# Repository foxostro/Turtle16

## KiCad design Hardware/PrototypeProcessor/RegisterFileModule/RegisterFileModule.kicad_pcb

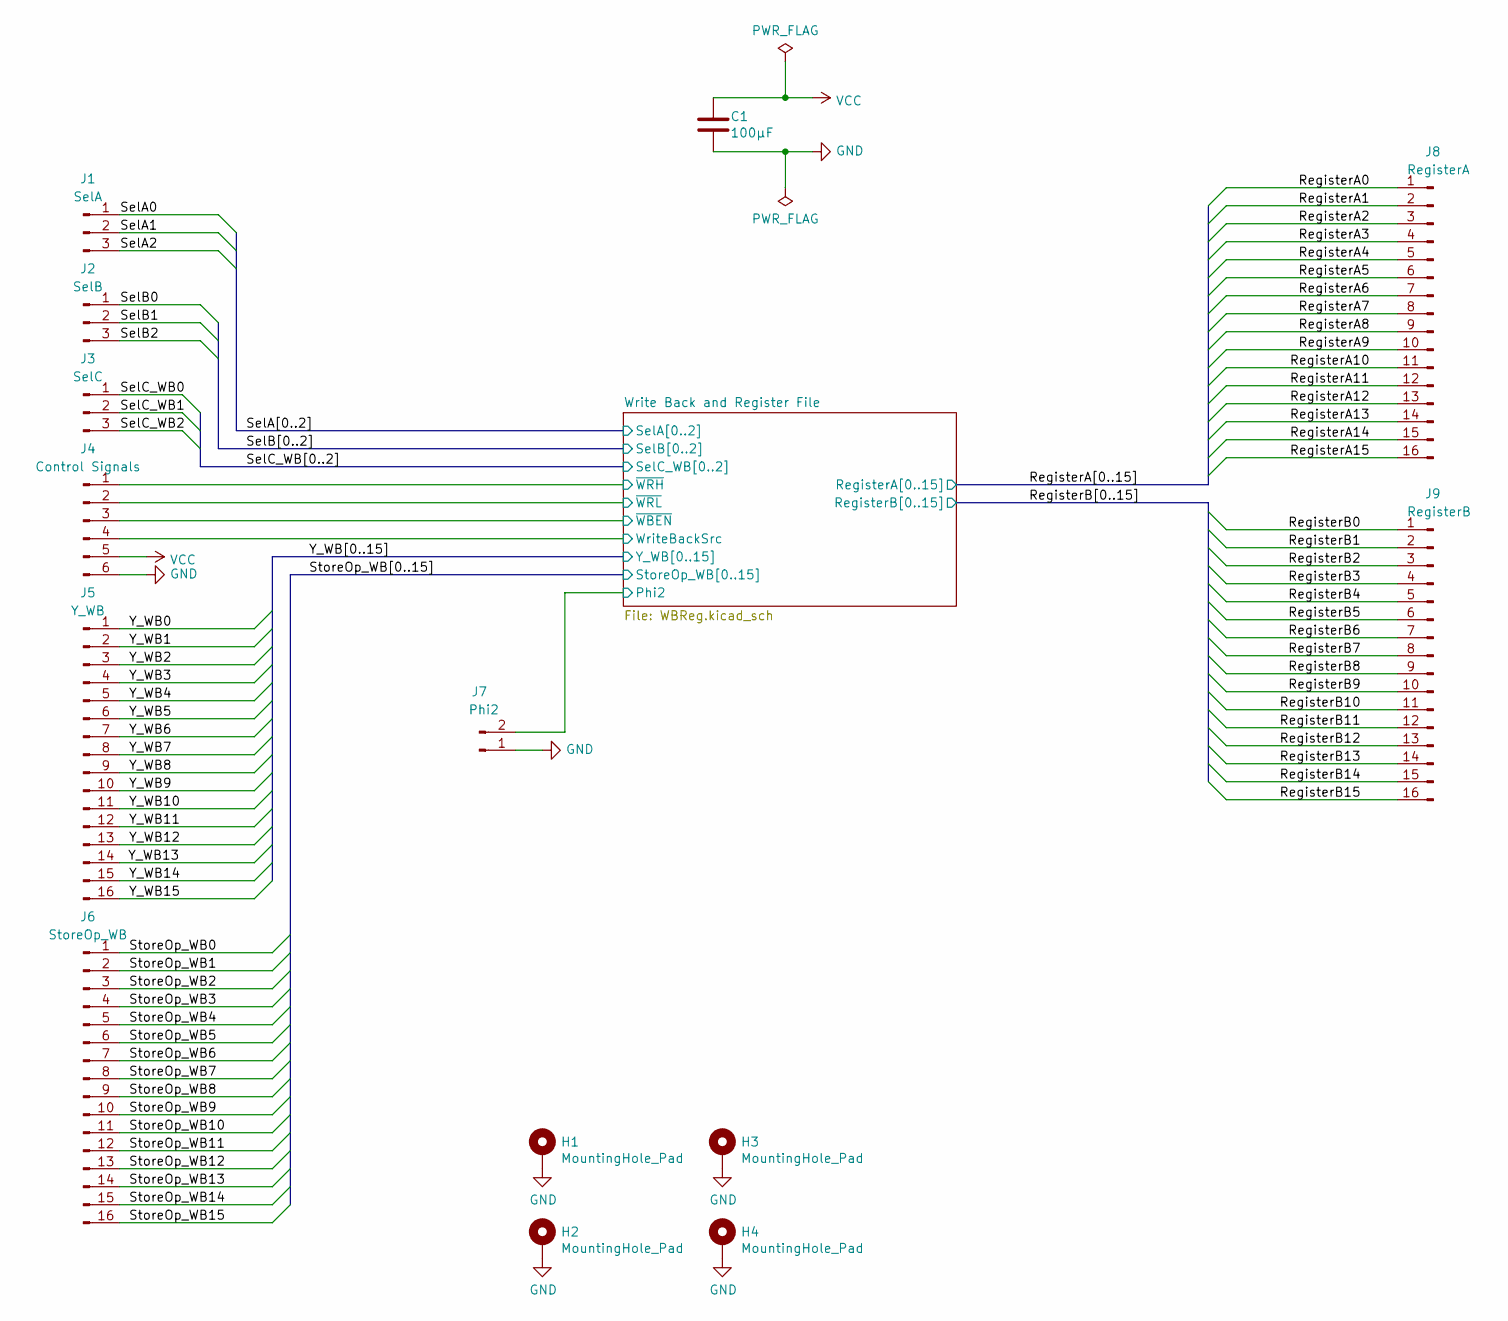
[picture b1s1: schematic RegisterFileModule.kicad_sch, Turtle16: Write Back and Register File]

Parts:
C1: 100µF; C_1206_3216Metric_Pad1.33x1.80mm_HandSolder
H1, H2, H3, H4: MountingHole_Pad; MountingHole_3.2mm_M3_Pad
J1: SelA; PinHeader_1x03_P2.54mm_Vertical
J2: SelB; PinHeader_1x03_P2.54mm_Vertical
J3: SelC; PinHeader_1x03_P2.54mm_Vertical
J4: Control Signals; PinHeader_1x06_P2.54mm_Vertical
J5: Y_WB; PinHeader_1x16_P2.54mm_Vertical
J6: StoreOp_WB; PinHeader_1x16_P2.54mm_Vertical
J7: Phi2; PinHeader_1x02_P2.54mm_Vertical
J8: RegisterA; PinHeader_1x16_P2.54mm_Vertical
J9: RegisterB; PinHeader_1x16_P2.54mm_Vertical

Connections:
/RegisterA0: J8.1; also elsewhere on the board
/RegisterA1: J8.2; also elsewhere on the board
/RegisterA2: J8.3; also elsewhere on the board
/RegisterA3: J8.4; also elsewhere on the board
/RegisterA4: J8.5; also elsewhere on the board
/RegisterA5: J8.6; also elsewhere on the board
/RegisterA6: J8.7; also elsewhere on the board
/RegisterA7: J8.8; also elsewhere on the board
/RegisterA8: J8.9; also elsewhere on the board
/RegisterA9: J8.10; also elsewhere on the board
/RegisterA10: J8.11; also elsewhere on the board
/RegisterA11: J8.12; also elsewhere on the board
/RegisterA12: J8.13; also elsewhere on the board
/RegisterA13: J8.14; also elsewhere on the board
/RegisterA14: J8.15; also elsewhere on the board
/RegisterA15: J8.16; also elsewhere on the board
/RegisterB0: J9.1; also elsewhere on the board
/RegisterB1: J9.2; also elsewhere on the board
/RegisterB2: J9.3; also elsewhere on the board
/RegisterB3: J9.4; also elsewhere on the board
/RegisterB4: J9.5; also elsewhere on the board
/RegisterB5: J9.6; also elsewhere on the board
/RegisterB6: J9.7; also elsewhere on the board
/RegisterB7: J9.8; also elsewhere on the board
/RegisterB8: J9.9; also elsewhere on the board
/RegisterB9: J9.10; also elsewhere on the board
/RegisterB10: J9.11; also elsewhere on the board
/RegisterB11: J9.12; also elsewhere on the board
/RegisterB12: J9.13; also elsewhere on the board
/RegisterB13: J9.14; also elsewhere on the board
/RegisterB14: J9.15; also elsewhere on the board
/RegisterB15: J9.16; also elsewhere on the board
/SelA0: J1.1; also elsewhere on the board
/SelA1: J1.2; also elsewhere on the board
/SelA2: J1.3; also elsewhere on the board
/SelB0: J2.1; also elsewhere on the board
/SelB1: J2.2; also elsewhere on the board
/SelB2: J2.3; also elsewhere on the board
/SelC_WB0: J3.1; also elsewhere on the board
/SelC_WB1: J3.2; also elsewhere on the board
/SelC_WB2: J3.3; also elsewhere on the board
/StoreOp_WB0: J6.1; also elsewhere on the board
/StoreOp_WB1: J6.2; also elsewhere on the board
/StoreOp_WB2: J6.3; also elsewhere on the board
/StoreOp_WB3: J6.4; also elsewhere on the board
/StoreOp_WB4: J6.5; also elsewhere on the board
/StoreOp_WB5: J6.6; also elsewhere on the board
/StoreOp_WB6: J6.7; also elsewhere on the board
/StoreOp_WB7: J6.8; also elsewhere on the board
/StoreOp_WB8: J6.9; also elsewhere on the board
/StoreOp_WB9: J6.10; also elsewhere on the board
/StoreOp_WB10: J6.11; also elsewhere on the board
/StoreOp_WB11: J6.12; also elsewhere on the board
/StoreOp_WB12: J6.13; also elsewhere on the board
/StoreOp_WB13: J6.14; also elsewhere on the board
/StoreOp_WB14: J6.15; also elsewhere on the board
/StoreOp_WB15: J6.16; also elsewhere on the board
/Write Back and Register File/Phi2: J7.2; also elsewhere on the board
/Write Back and Register File/WriteBackSrc: J4.4; also elsewhere on the board
/Write Back and Register File/~WBEN: J4.3; also elsewhere on the board
/Write Back and Register File/~WRH: J4.1; also elsewhere on the board
/Write Back and Register File/~WRL: J4.2; also elsewhere on the board
/Y_WB0: J5.1; also elsewhere on the board
/Y_WB1: J5.2; also elsewhere on the board
/Y_WB2: J5.3; also elsewhere on the board
/Y_WB3: J5.4; also elsewhere on the board
/Y_WB4: J5.5; also elsewhere on the board
/Y_WB5: J5.6; also elsewhere on the board
/Y_WB6: J5.7; also elsewhere on the board
/Y_WB7: J5.8; also elsewhere on the board
/Y_WB8: J5.9; also elsewhere on the board
/Y_WB9: J5.10; also elsewhere on the board
/Y_WB10: J5.11; also elsewhere on the board
/Y_WB11: J5.12; also elsewhere on the board
/Y_WB12: J5.13; also elsewhere on the board
/Y_WB13: J5.14; also elsewhere on the board
/Y_WB14: J5.15; also elsewhere on the board
/Y_WB15: J5.16; also elsewhere on the board
GND: C1.2, H1.1, H2.1, H3.1, H4.1, J4.6, J7.1; also elsewhere on the board
VCC: C1.1, J4.5; also elsewhere on the board

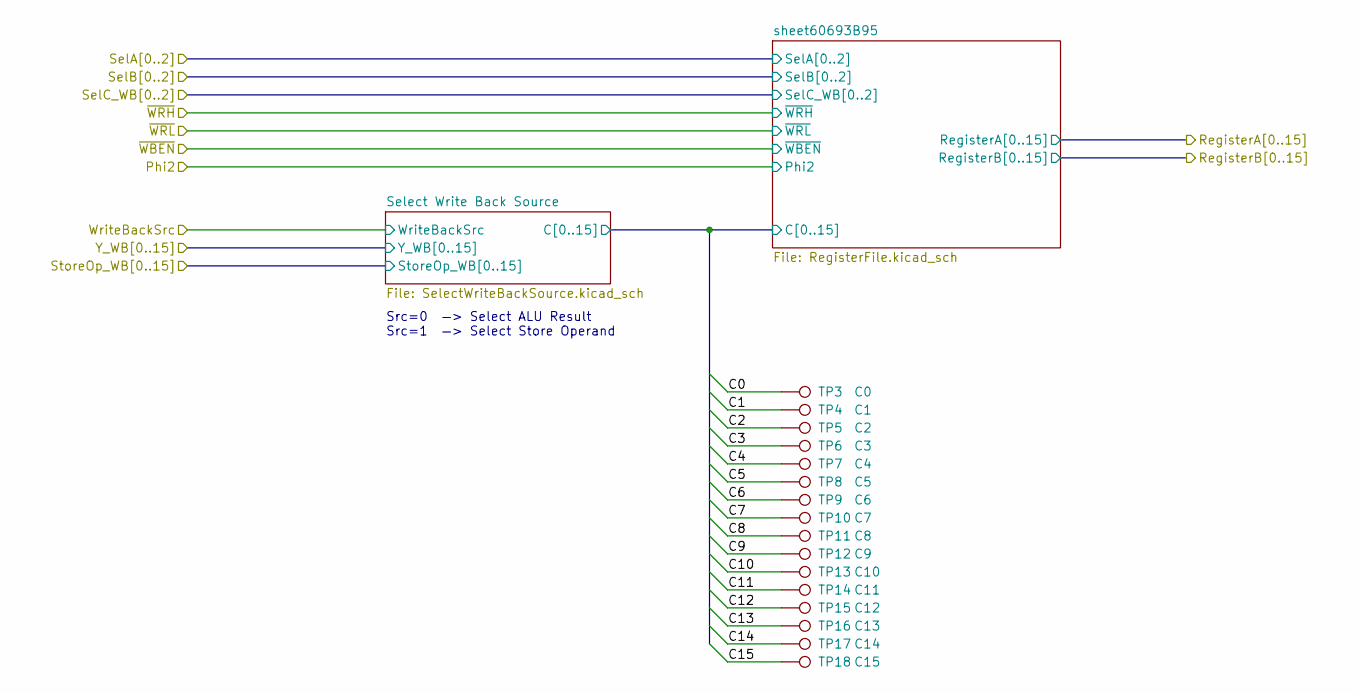
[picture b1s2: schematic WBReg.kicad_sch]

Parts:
TP3: C0; TestPoint_Pad_D1.0mm
TP4: C1; TestPoint_Pad_D1.0mm
TP5: C2; TestPoint_Pad_D1.0mm
TP6: C3; TestPoint_Pad_D1.0mm
TP7: C4; TestPoint_Pad_D1.0mm
TP8: C5; TestPoint_Pad_D1.0mm
TP9: C6; TestPoint_Pad_D1.0mm
TP10: C7; TestPoint_Pad_D1.0mm
TP11: C8; TestPoint_Pad_D1.0mm
TP12: C9; TestPoint_Pad_D1.0mm
TP13: C10; TestPoint_Pad_D1.0mm
TP14: C11; TestPoint_Pad_D1.0mm
TP15: C12; TestPoint_Pad_D1.0mm
TP16: C13; TestPoint_Pad_D1.0mm
TP17: C14; TestPoint_Pad_D1.0mm
TP18: C15; TestPoint_Pad_D1.0mm

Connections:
/Write Back and Register File/Select Write Back Source/C0: TP3.1; also elsewhere on the board
/Write Back and Register File/Select Write Back Source/C1: TP4.1; also elsewhere on the board
/Write Back and Register File/Select Write Back Source/C2: TP5.1; also elsewhere on the board
/Write Back and Register File/Select Write Back Source/C3: TP6.1; also elsewhere on the board
/Write Back and Register File/Select Write Back Source/C4: TP7.1; also elsewhere on the board
/Write Back and Register File/Select Write Back Source/C5: TP8.1; also elsewhere on the board
/Write Back and Register File/Select Write Back Source/C6: TP9.1; also elsewhere on the board
/Write Back and Register File/Select Write Back Source/C7: TP10.1; also elsewhere on the board
/Write Back and Register File/Select Write Back Source/C8: TP11.1; also elsewhere on the board
/Write Back and Register File/Select Write Back Source/C9: TP12.1; also elsewhere on the board
/Write Back and Register File/Select Write Back Source/C10: TP13.1; also elsewhere on the board
/Write Back and Register File/Select Write Back Source/C11: TP14.1; also elsewhere on the board
/Write Back and Register File/Select Write Back Source/C12: TP15.1; also elsewhere on the board
/Write Back and Register File/Select Write Back Source/C13: TP16.1; also elsewhere on the board
/Write Back and Register File/Select Write Back Source/C14: TP17.1; also elsewhere on the board
/Write Back and Register File/Select Write Back Source/C15: TP18.1; also elsewhere on the board

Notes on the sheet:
Src=0 —> Select ALU Result Src=1 —> Select Store Operand

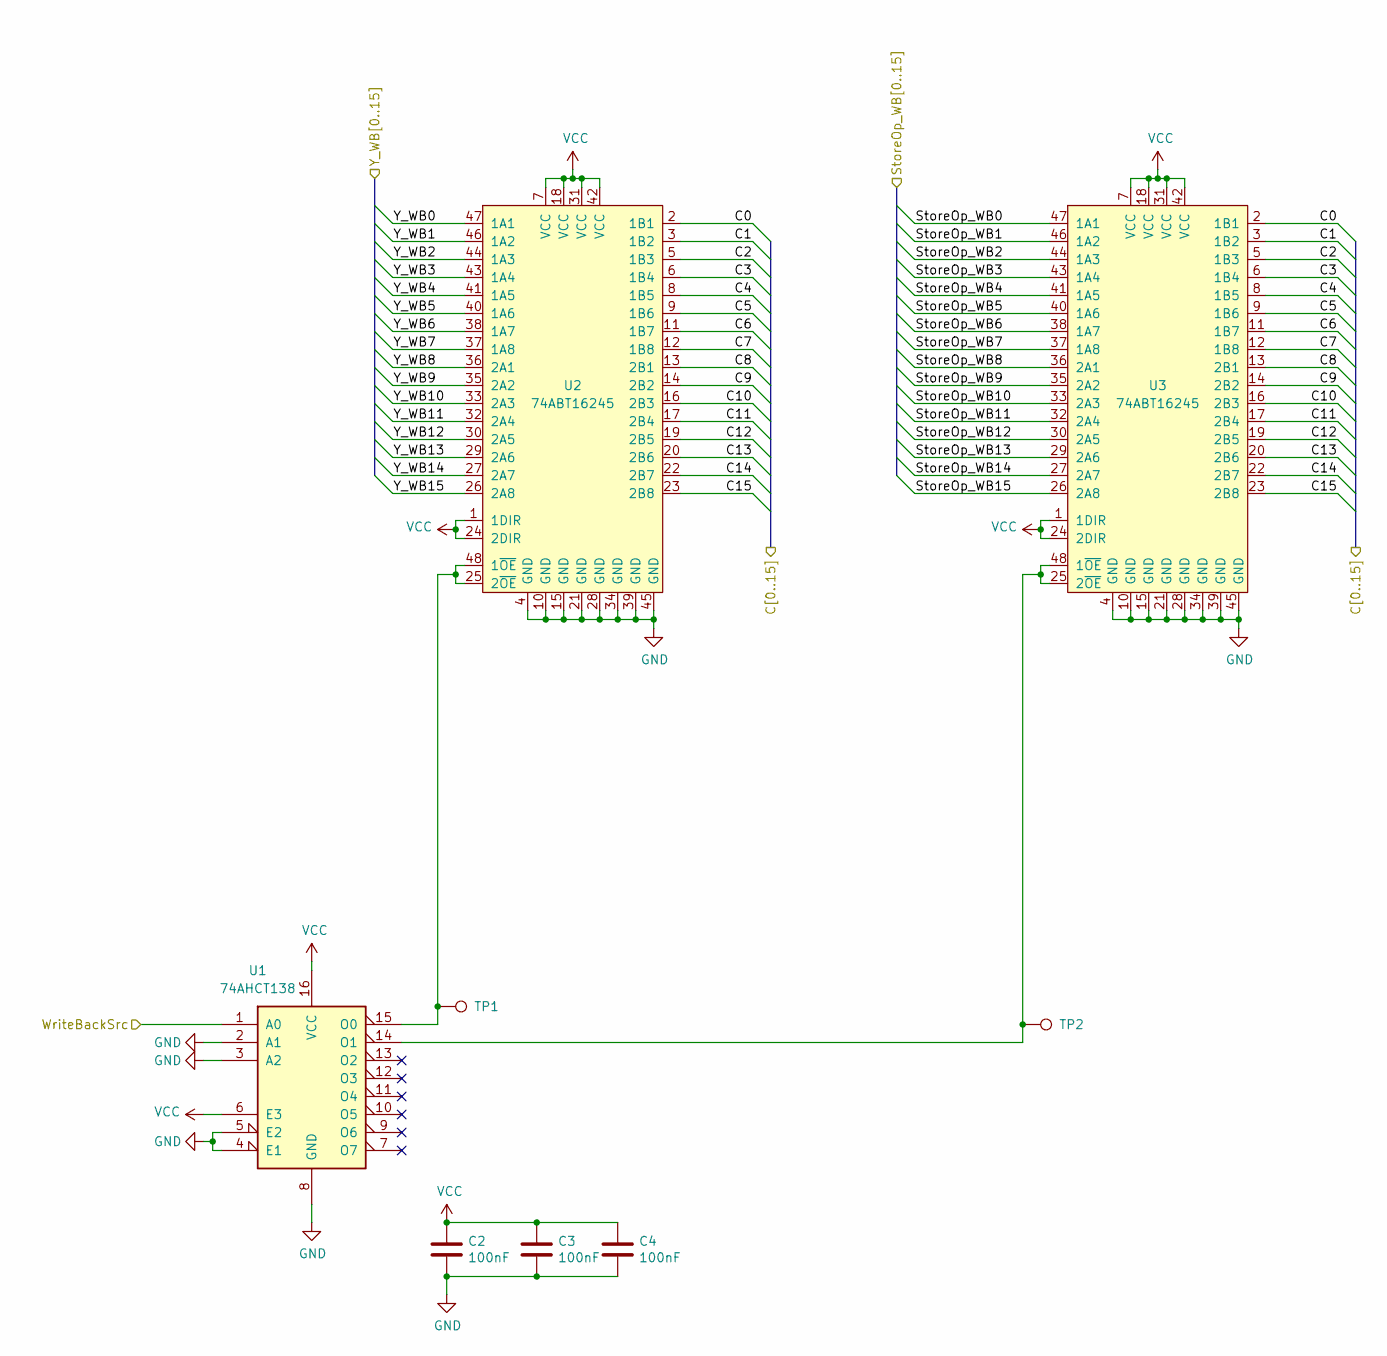
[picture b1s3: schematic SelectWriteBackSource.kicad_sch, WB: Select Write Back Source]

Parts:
C2, C3, C4: 100nF; C_0603_1608Metric_Pad1.08x0.95mm_HandSolder
TP1, TP2: TP; TestPoint_Pad_D1.0mm
U1: 74AHCT138; TSSOP-16_4.4x5mm_P0.65mm
U2, U3: 74ABT16245; TSSOP-48_6.1x12.5mm_P0.5mm

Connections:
/StoreOp_WB0: U3.47 (1A1); also elsewhere on the board
/StoreOp_WB1: U3.46 (1A2); also elsewhere on the board
/StoreOp_WB2: U3.44 (1A3); also elsewhere on the board
/StoreOp_WB3: U3.43 (1A4); also elsewhere on the board
/StoreOp_WB4: U3.41 (1A5); also elsewhere on the board
/StoreOp_WB5: U3.40 (1A6); also elsewhere on the board
/StoreOp_WB6: U3.38 (1A7); also elsewhere on the board
/StoreOp_WB7: U3.37 (1A8); also elsewhere on the board
/StoreOp_WB8: U3.36 (2A1); also elsewhere on the board
/StoreOp_WB9: U3.35 (2A2); also elsewhere on the board
/StoreOp_WB10: U3.33 (2A3); also elsewhere on the board
/StoreOp_WB11: U3.32 (2A4); also elsewhere on the board
/StoreOp_WB12: U3.30 (2A5); also elsewhere on the board
/StoreOp_WB13: U3.29 (2A6); also elsewhere on the board
/StoreOp_WB14: U3.27 (2A7); also elsewhere on the board
/StoreOp_WB15: U3.26 (2A8); also elsewhere on the board
/Write Back and Register File/Select Write Back Source/C0: U2.2 (1B1), U3.2 (1B1); also elsewhere on the board
/Write Back and Register File/Select Write Back Source/C1: U2.3 (1B2), U3.3 (1B2); also elsewhere on the board
/Write Back and Register File/Select Write Back Source/C2: U2.5 (1B3), U3.5 (1B3); also elsewhere on the board
/Write Back and Register File/Select Write Back Source/C3: U2.6 (1B4), U3.6 (1B4); also elsewhere on the board
/Write Back and Register File/Select Write Back Source/C4: U2.8 (1B5), U3.8 (1B5); also elsewhere on the board
/Write Back and Register File/Select Write Back Source/C5: U2.9 (1B6), U3.9 (1B6); also elsewhere on the board
/Write Back and Register File/Select Write Back Source/C6: U2.11 (1B7), U3.11 (1B7); also elsewhere on the board
/Write Back and Register File/Select Write Back Source/C7: U2.12 (1B8), U3.12 (1B8); also elsewhere on the board
/Write Back and Register File/Select Write Back Source/C8: U2.13 (2B1), U3.13 (2B1); also elsewhere on the board
/Write Back and Register File/Select Write Back Source/C9: U2.14 (2B2), U3.14 (2B2); also elsewhere on the board
/Write Back and Register File/Select Write Back Source/C10: U2.16 (2B3), U3.16 (2B3); also elsewhere on the board
/Write Back and Register File/Select Write Back Source/C11: U2.17 (2B4), U3.17 (2B4); also elsewhere on the board
/Write Back and Register File/Select Write Back Source/C12: U2.19 (2B5), U3.19 (2B5); also elsewhere on the board
/Write Back and Register File/Select Write Back Source/C13: U2.20 (2B6), U3.20 (2B6); also elsewhere on the board
/Write Back and Register File/Select Write Back Source/C14: U2.22 (2B7), U3.22 (2B7); also elsewhere on the board
/Write Back and Register File/Select Write Back Source/C15: U2.23 (2B8), U3.23 (2B8); also elsewhere on the board
/Write Back and Register File/WriteBackSrc: U1.1 (A0); also elsewhere on the board
/Y_WB0: U2.47 (1A1); also elsewhere on the board
/Y_WB1: U2.46 (1A2); also elsewhere on the board
/Y_WB2: U2.44 (1A3); also elsewhere on the board
/Y_WB3: U2.43 (1A4); also elsewhere on the board
/Y_WB4: U2.41 (1A5); also elsewhere on the board
/Y_WB5: U2.40 (1A6); also elsewhere on the board
/Y_WB6: U2.38 (1A7); also elsewhere on the board
/Y_WB7: U2.37 (1A8); also elsewhere on the board
/Y_WB8: U2.36 (2A1); also elsewhere on the board
/Y_WB9: U2.35 (2A2); also elsewhere on the board
/Y_WB10: U2.33 (2A3); also elsewhere on the board
/Y_WB11: U2.32 (2A4); also elsewhere on the board
/Y_WB12: U2.30 (2A5); also elsewhere on the board
/Y_WB13: U2.29 (2A6); also elsewhere on the board
/Y_WB14: U2.27 (2A7); also elsewhere on the board
/Y_WB15: U2.26 (2A8); also elsewhere on the board
GND: C2.2, C3.2, C4.2, U1.2 (A1), U1.3 (A2), U1.4 (E1), U1.5 (E2), U1.8 (GND), U2.4 (GND), U2.10 (GND), U2.15 (GND), U2.21 (GND), U2.28 (GND), U2.34 (GND), U2.39 (GND), U2.45 (GND), U3.4 (GND), U3.10 (GND), U3.15 (GND), U3.21 (GND), U3.28 (GND), U3.34 (GND), U3.39 (GND), U3.45 (GND); also elsewhere on the board
unnamed: TP1.1, U1.15 (O0), U2.25 (2~OE), U2.48 (1~OE)
unnamed: TP2.1, U1.14 (O1), U3.25 (2~OE), U3.48 (1~OE)
VCC: C2.1, C3.1, C4.1, U1.6 (E3), U1.16 (VCC), U2.1 (1DIR), U2.7 (VCC), U2.18 (VCC), U2.24 (2DIR), U2.31 (VCC), U2.42 (VCC), U3.1 (1DIR), U3.7 (VCC), U3.18 (VCC), U3.24 (2DIR), U3.31 (VCC), U3.42 (VCC); also elsewhere on the board

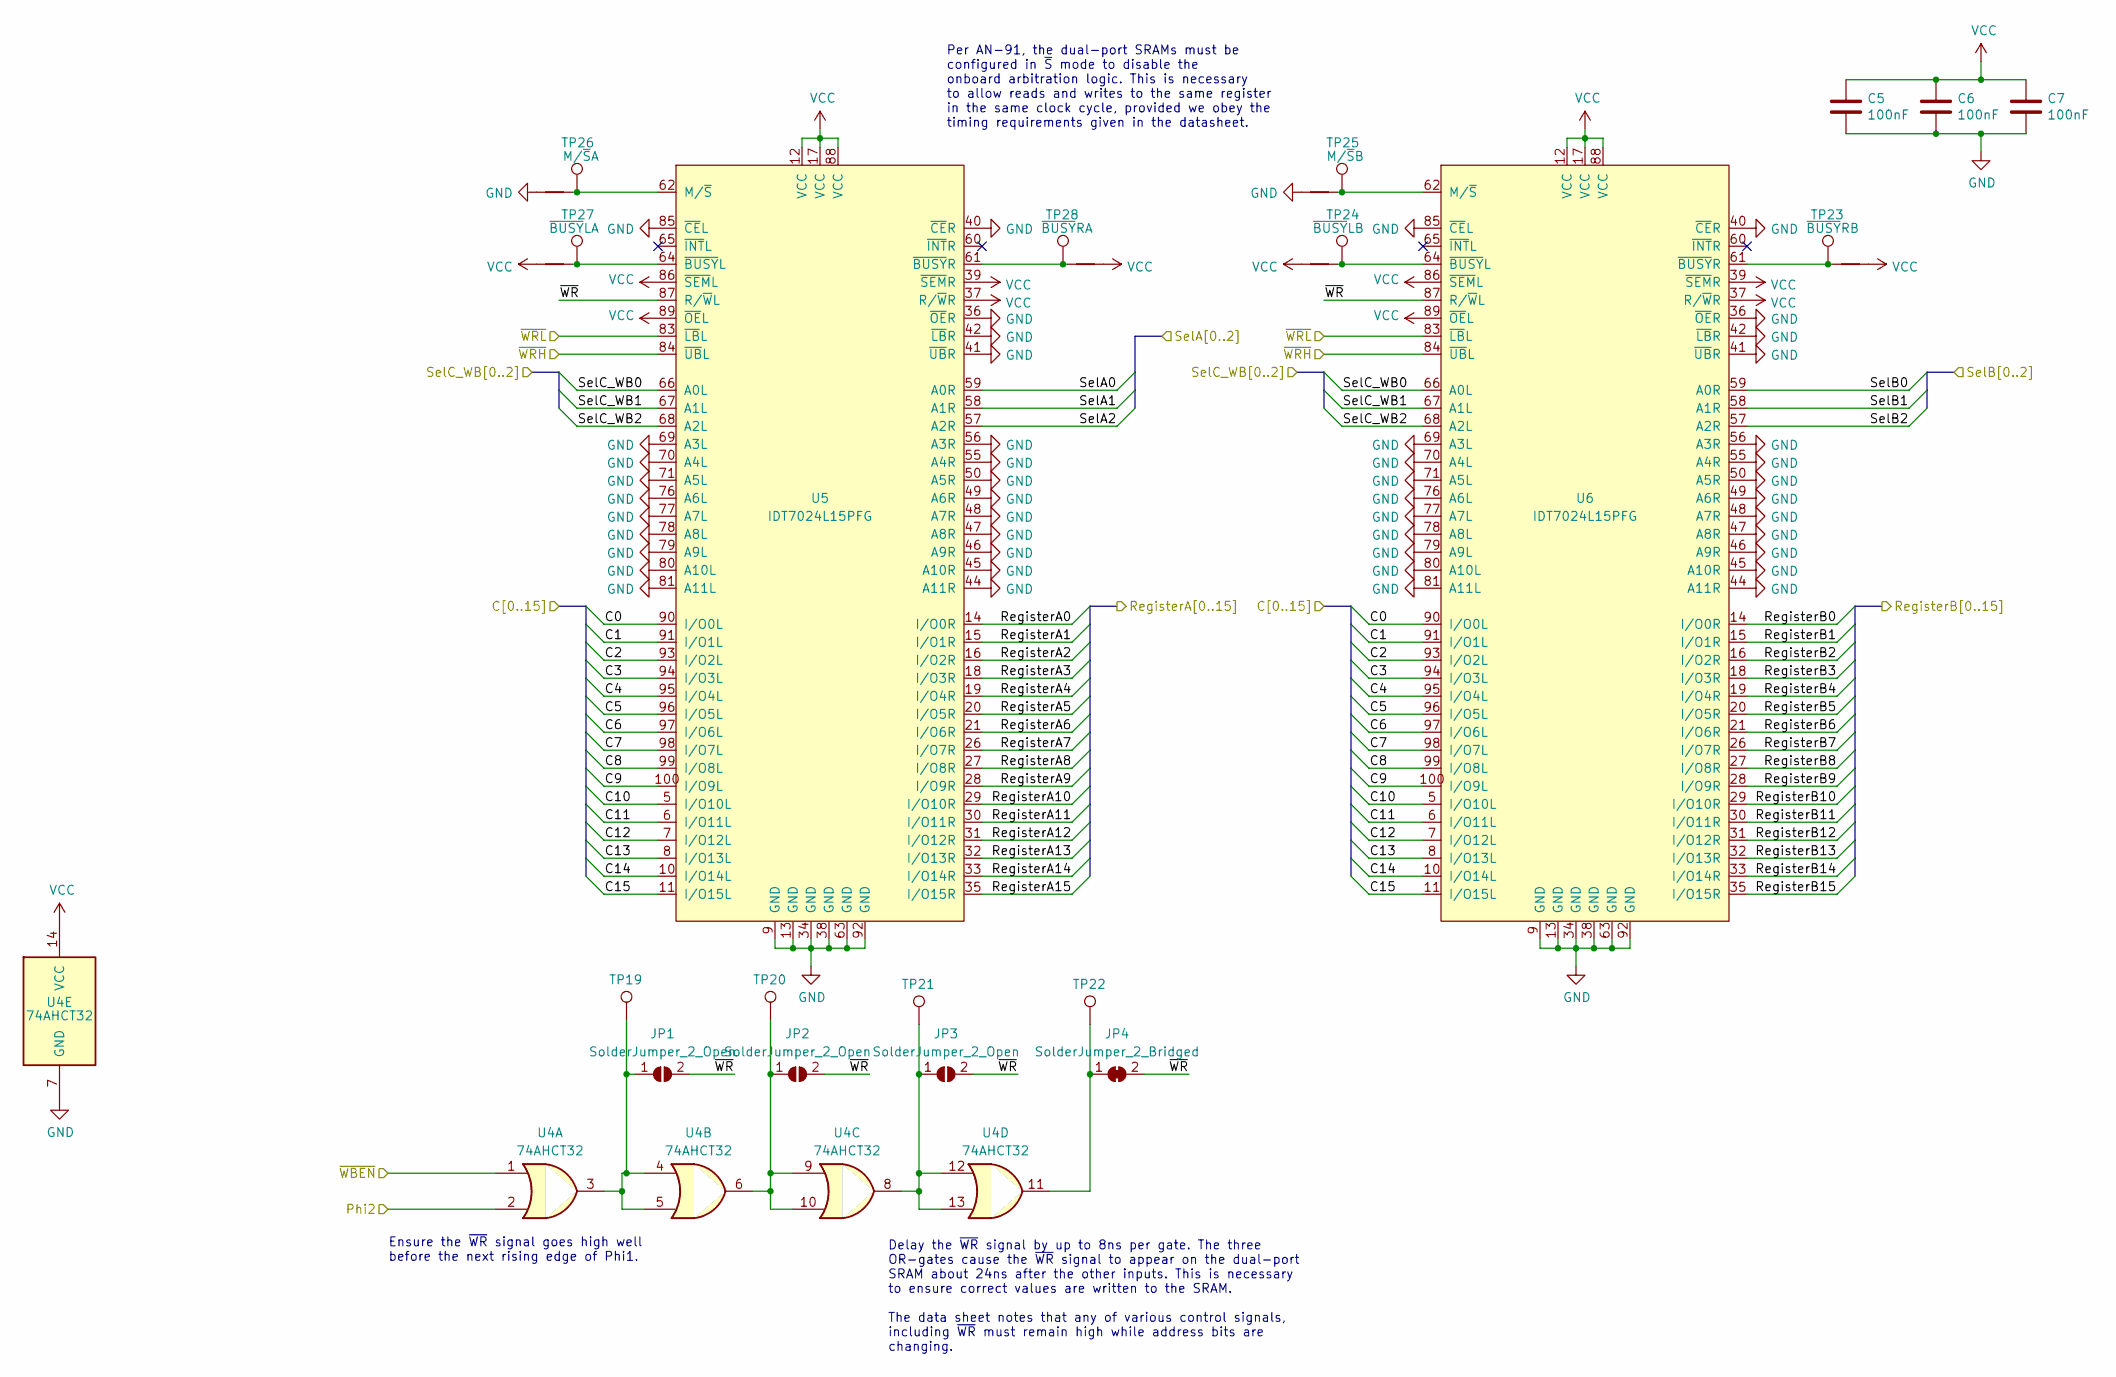
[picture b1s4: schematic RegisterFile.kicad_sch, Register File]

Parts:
C5, C6, C7: 100nF; C_0603_1608Metric_Pad1.08x0.95mm_HandSolder
JP1, JP2, JP3: SolderJumper_2_Open; SolderJumper-2_P1.3mm_Open_RoundedPad1.0x1.5mm
JP4: SolderJumper_2_Bridged; SolderJumper-2_P1.3mm_Bridged2Bar_RoundedPad1.0x1.5mm
NT1, NT2, NT3, NT4, NT5, NT6: NetTie_2; NetTie-2_SMD_Pad0.5mm
TP19, TP20, TP21, TP22: TP; TestPoint_Pad_D1.0mm
TP23: ~{BUSY}RB; TestPoint_Pad_D1.0mm
TP24: ~{BUSY}LB; TestPoint_Pad_D1.0mm
TP25: M/~{S}B; TestPoint_Pad_D1.0mm
TP26: M/~{S}A; TestPoint_Pad_D1.0mm
TP27: ~{BUSY}LA; TestPoint_Pad_D1.0mm
TP28: ~{BUSY}RA; TestPoint_Pad_D1.0mm
U4: 74AHCT32; TSSOP-14_4.4x5mm_P0.65mm
U5, U6: IDT7024L15PFG; TQFP-100_14x14mm_P0.5mm

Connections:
/RegisterA0: U5.14 (I/O0R); also elsewhere on the board
/RegisterA1: U5.15 (I/O1R); also elsewhere on the board
/RegisterA2: U5.16 (I/O2R); also elsewhere on the board
/RegisterA3: U5.18 (I/O3R); also elsewhere on the board
/RegisterA4: U5.19 (I/O4R); also elsewhere on the board
/RegisterA5: U5.20 (I/O5R); also elsewhere on the board
/RegisterA6: U5.21 (I/O6R); also elsewhere on the board
/RegisterA7: U5.26 (I/O7R); also elsewhere on the board
/RegisterA8: U5.27 (I/O8R); also elsewhere on the board
/RegisterA9: U5.28 (I/O9R); also elsewhere on the board
/RegisterA10: U5.29 (I/O10R); also elsewhere on the board
/RegisterA11: U5.30 (I/O11R); also elsewhere on the board
/RegisterA12: U5.31 (I/O12R); also elsewhere on the board
/RegisterA13: U5.32 (I/O13R); also elsewhere on the board
/RegisterA14: U5.33 (I/O14R); also elsewhere on the board
/RegisterA15: U5.35 (I/O15R); also elsewhere on the board
/RegisterB0: U6.14 (I/O0R); also elsewhere on the board
/RegisterB1: U6.15 (I/O1R); also elsewhere on the board
/RegisterB2: U6.16 (I/O2R); also elsewhere on the board
/RegisterB3: U6.18 (I/O3R); also elsewhere on the board
/RegisterB4: U6.19 (I/O4R); also elsewhere on the board
/RegisterB5: U6.20 (I/O5R); also elsewhere on the board
/RegisterB6: U6.21 (I/O6R); also elsewhere on the board
/RegisterB7: U6.26 (I/O7R); also elsewhere on the board
/RegisterB8: U6.27 (I/O8R); also elsewhere on the board
/RegisterB9: U6.28 (I/O9R); also elsewhere on the board
/RegisterB10: U6.29 (I/O10R); also elsewhere on the board
/RegisterB11: U6.30 (I/O11R); also elsewhere on the board
/RegisterB12: U6.31 (I/O12R); also elsewhere on the board
/RegisterB13: U6.32 (I/O13R); also elsewhere on the board
/RegisterB14: U6.33 (I/O14R); also elsewhere on the board
/RegisterB15: U6.35 (I/O15R); also elsewhere on the board
/SelA0: U5.59 (A0R); also elsewhere on the board
/SelA1: U5.58 (A1R); also elsewhere on the board
/SelA2: U5.57 (A2R); also elsewhere on the board
/SelB0: U6.59 (A0R); also elsewhere on the board
/SelB1: U6.58 (A1R); also elsewhere on the board
/SelB2: U6.57 (A2R); also elsewhere on the board
/SelC_WB0: U5.66 (A0L), U6.66 (A0L); also elsewhere on the board
/SelC_WB1: U5.67 (A1L), U6.67 (A1L); also elsewhere on the board
/SelC_WB2: U5.68 (A2L), U6.68 (A2L); also elsewhere on the board
/Write Back and Register File/Phi2: U4.2; also elsewhere on the board
/Write Back and Register File/Select Write Back Source/C0: U5.90 (I/O0L), U6.90 (I/O0L); also elsewhere on the board
/Write Back and Register File/Select Write Back Source/C1: U5.91 (I/O1L), U6.91 (I/O1L); also elsewhere on the board
/Write Back and Register File/Select Write Back Source/C2: U5.93 (I/O2L), U6.93 (I/O2L); also elsewhere on the board
/Write Back and Register File/Select Write Back Source/C3: U5.94 (I/O3L), U6.94 (I/O3L); also elsewhere on the board
/Write Back and Register File/Select Write Back Source/C4: U5.95 (I/O4L), U6.95 (I/O4L); also elsewhere on the board
/Write Back and Register File/Select Write Back Source/C5: U5.96 (I/O5L), U6.96 (I/O5L); also elsewhere on the board
/Write Back and Register File/Select Write Back Source/C6: U5.97 (I/O6L), U6.97 (I/O6L); also elsewhere on the board
/Write Back and Register File/Select Write Back Source/C7: U5.98 (I/O7L), U6.98 (I/O7L); also elsewhere on the board
/Write Back and Register File/Select Write Back Source/C8: U5.99 (I/O8L), U6.99 (I/O8L); also elsewhere on the board
/Write Back and Register File/Select Write Back Source/C9: U5.100 (I/O9L), U6.100 (I/O9L); also elsewhere on the board
/Write Back and Register File/Select Write Back Source/C10: U5.5 (I/O10L), U6.5 (I/O10L); also elsewhere on the board
/Write Back and Register File/Select Write Back Source/C11: U5.6 (I/O11L), U6.6 (I/O11L); also elsewhere on the board
/Write Back and Register File/Select Write Back Source/C12: U5.7 (I/O12L), U6.7 (I/O12L); also elsewhere on the board
/Write Back and Register File/Select Write Back Source/C13: U5.8 (I/O13L), U6.8 (I/O13L); also elsewhere on the board
/Write Back and Register File/Select Write Back Source/C14: U5.10 (I/O14L), U6.10 (I/O14L); also elsewhere on the board
/Write Back and Register File/Select Write Back Source/C15: U5.11 (I/O15L), U6.11 (I/O15L); also elsewhere on the board
/Write Back and Register File/sheet60693B95/~WR: JP1.2 (B), JP2.2 (B), JP3.2 (B), JP4.2 (B), U5.87 (R/~WL), U6.87 (R/~WL)
/Write Back and Register File/~WBEN: U4.1; also elsewhere on the board
/Write Back and Register File/~WRH: U5.84 (~UBL), U6.84 (~UBL); also elsewhere on the board
/Write Back and Register File/~WRL: U5.83 (~LBL), U6.83 (~LBL); also elsewhere on the board
GND: C5.2, C6.2, C7.2, NT1.1, NT4.1, U4.7 (GND), U5.9 (GND), U5.13 (GND), U5.34 (GND), U5.36 (~OER), U5.38 (GND), U5.40 (~CER), U5.41 (~UBR), U5.42 (~LBR), U5.44 (A11R), U5.45 (A10R), U5.46 (A9R), U5.47 (A8R), U5.48 (A7R), U5.49 (A6R), U5.50 (A5R), U5.55 (A4R), U5.56 (A3R), U5.63 (GND), U5.69 (A3L), U5.70 (A4L), U5.71 (A5L), U5.76 (A6L), U5.77 (A7L), U5.78 (A8L), U5.79 (A9L), U5.80 (A10L), U5.81 (A11L), U5.85 (~CEL), U5.92 (GND), U6.9 (GND), U6.13 (GND), U6.34 (GND), U6.36 (~OER), U6.38 (GND), U6.40 (~CER), U6.41 (~UBR), U6.42 (~LBR), U6.44 (A11R), U6.45 (A10R), U6.46 (A9R), U6.47 (A8R), U6.48 (A7R), U6.49 (A6R), U6.50 (A5R), U6.55 (A4R), U6.56 (A3R), U6.63 (GND), U6.69 (A3L), U6.70 (A4L), U6.71 (A5L), U6.76 (A6L), U6.77 (A7L), U6.78 (A8L), U6.79 (A9L), U6.80 (A10L), U6.81 (A11L), U6.85 (~CEL), U6.92 (GND); also elsewhere on the board
unnamed: JP1.1 (A), TP19.1, U4.3, U4.4, U4.5
unnamed: JP2.1 (A), TP20.1, U4.6, U4.9, U4.10
unnamed: JP3.1 (A), TP21.1, U4.8, U4.12, U4.13
unnamed: JP4.1 (A), TP22.1, U4.11
unnamed: NT1.2, TP26.1, U5.62 (M/~S)
unnamed: NT2.2, TP27.1, U5.64 (~BUSYL)
unnamed: NT3.2, TP28.1, U5.61 (~BUSYR)
unnamed: NT4.2, TP25.1, U6.62 (M/~S)
unnamed: NT5.2, TP24.1, U6.64 (~BUSYL)
unnamed: NT6.2, TP23.1, U6.61 (~BUSYR)
VCC: C5.1, C6.1, C7.1, NT2.1, NT3.1, NT5.1, NT6.1, U4.14 (VCC), U5.12 (VCC), U5.17 (VCC), U5.37 (R/~WR), U5.39 (~SEMR), U5.86 (~SEML), U5.88 (VCC), U5.89 (~OEL), U6.12 (VCC), U6.17 (VCC), U6.37 (R/~WR), U6.39 (~SEMR), U6.86 (~SEML), U6.88 (VCC), U6.89 (~OEL); also elsewhere on the board

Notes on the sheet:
Delay the ~{WR} signal by up to 8ns per gate. The three OR-gates cause the ~{WR} signal to appear on the dual-port SRAM about 24ns after the other inputs. This is necessary to ensure correct values are written to the SRAM. The data sheet notes that any of various control signals, including ~{WR} mu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
Per AN-91, the dual-port SRAMs must be configured in ~{S} mode to disable the onboard arbitration logic. This is necessary to allow reads and writes to the same register in the same clock cycle, provided we obey the timing requirements given in the datasheet.
Ensure the ~{WR} signal goes high well before the next rising edge of Phi1.

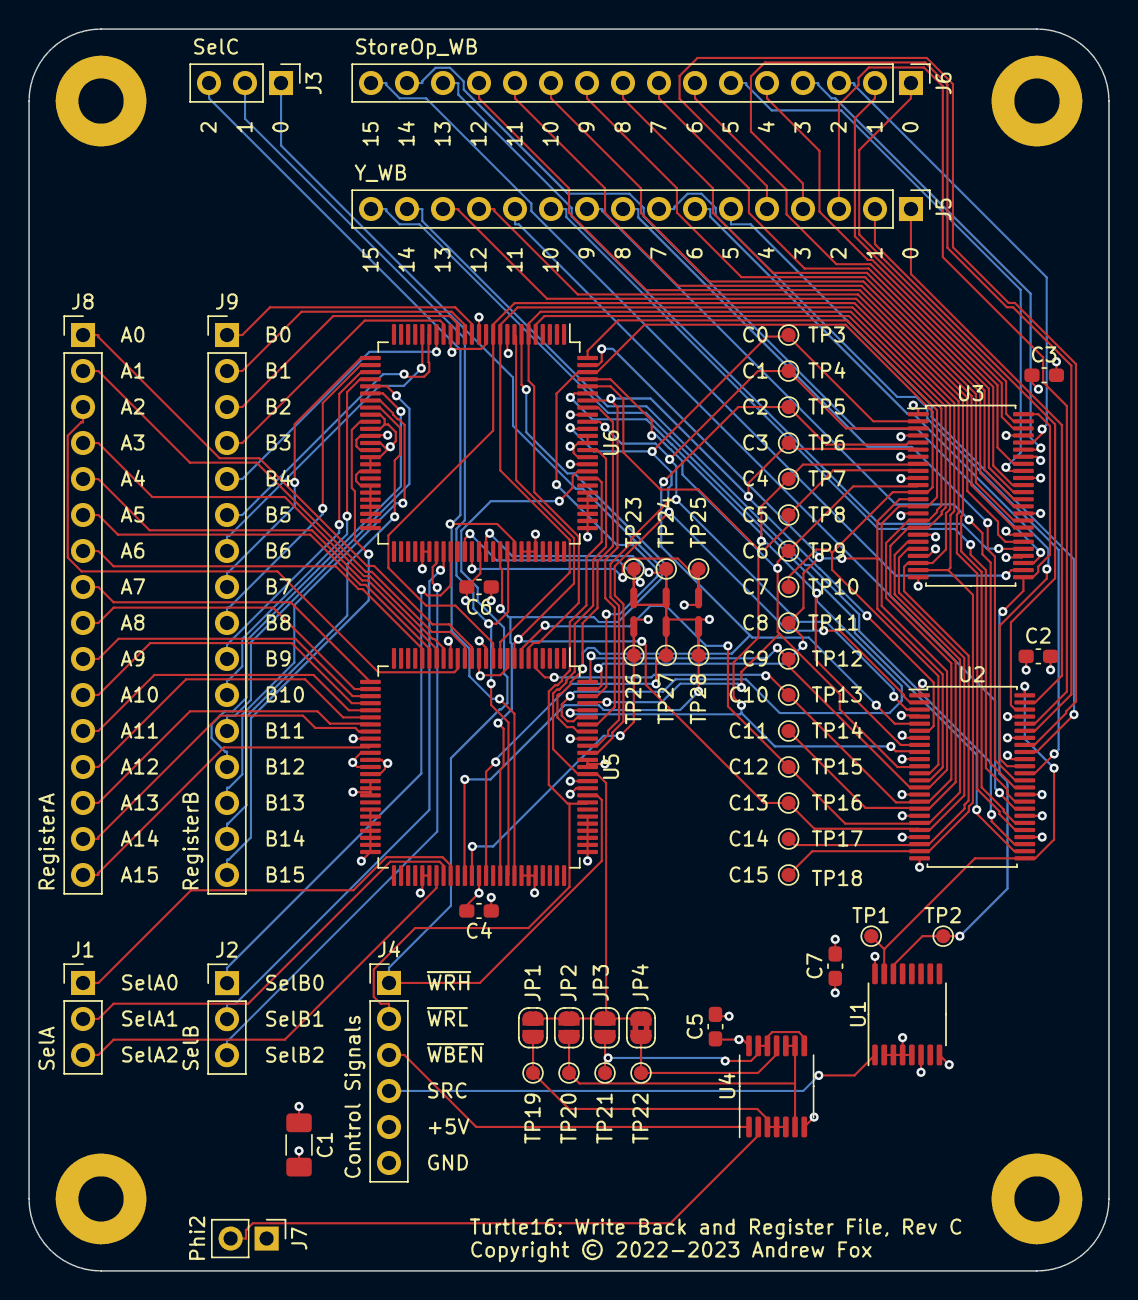
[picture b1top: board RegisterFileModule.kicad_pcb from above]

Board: 4 copper layers, 76.2 x 87.6 mm, 64 parts (0 on the bottom side), 109 nets.

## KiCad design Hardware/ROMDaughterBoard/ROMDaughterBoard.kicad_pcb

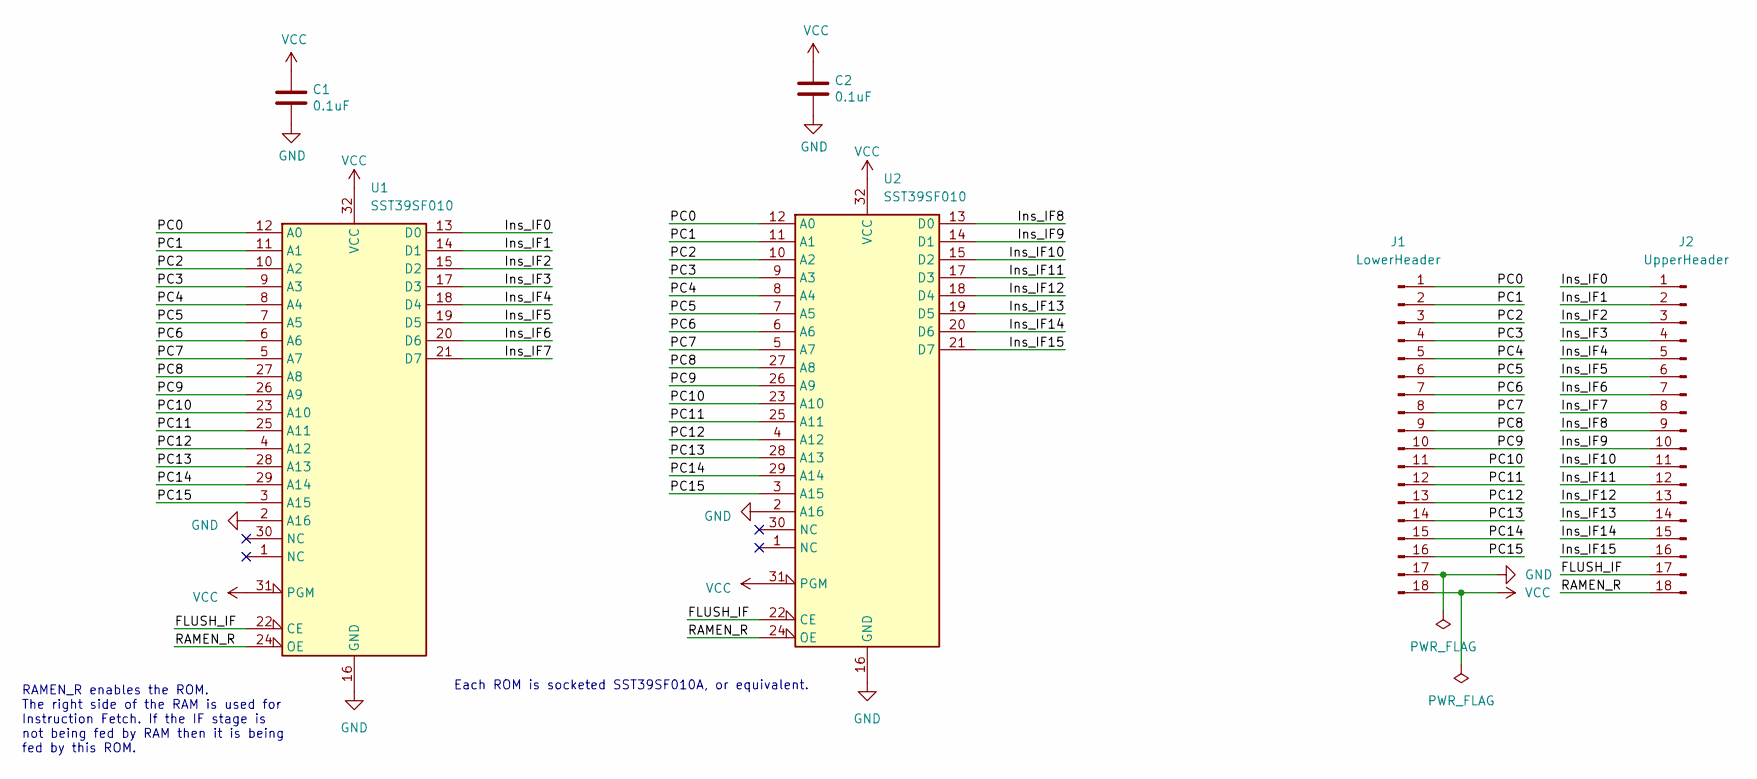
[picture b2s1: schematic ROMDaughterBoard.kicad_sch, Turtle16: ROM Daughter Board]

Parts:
C1, C2: 0.1uF; C_0603_1608Metric; Manufacturer# EMK107B7104KAHT; Mouser# 963-EMK107B7104KAHT
J1: LowerHeader; PinHeader_1x18_P2.54mm_Vertical
J2: UpperHeader; PinHeader_1x18_P2.54mm_Vertical
U1, U2: SST39SF010; 843221B1RKTP; Manufacturer# 8432-21B1-RK-TP; Mouser# 517-8432-21B1-RK-TP

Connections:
/FLUSH_IF: J2.17, U1.22 (CE), U2.22 (CE)
/Ins_IF0: J2.1, U1.13 (D0)
/Ins_IF1: J2.2, U1.14 (D1)
/Ins_IF2: J2.3, U1.15 (D2)
/Ins_IF3: J2.4, U1.17 (D3)
/Ins_IF4: J2.5, U1.18 (D4)
/Ins_IF5: J2.6, U1.19 (D5)
/Ins_IF6: J2.7, U1.20 (D6)
/Ins_IF7: J2.8, U1.21 (D7)
/Ins_IF8: J2.9, U2.13 (D0)
/Ins_IF9: J2.10, U2.14 (D1)
/Ins_IF10: J2.11, U2.15 (D2)
/Ins_IF11: J2.12, U2.17 (D3)
/Ins_IF12: J2.13, U2.18 (D4)
/Ins_IF13: J2.14, U2.19 (D5)
/Ins_IF14: J2.15, U2.20 (D6)
/Ins_IF15: J2.16, U2.21 (D7)
/PC0: J1.1, U1.12 (A0), U2.12 (A0)
/PC1: J1.2, U1.11 (A1), U2.11 (A1)
/PC2: J1.3, U1.10 (A2), U2.10 (A2)
/PC3: J1.4, U1.9 (A3), U2.9 (A3)
/PC4: J1.5, U1.8 (A4), U2.8 (A4)
/PC5: J1.6, U1.7 (A5), U2.7 (A5)
/PC6: J1.7, U1.6 (A6), U2.6 (A6)
/PC7: J1.8, U1.5 (A7), U2.5 (A7)
/PC8: J1.9, U1.27 (A8), U2.27 (A8)
/PC9: J1.10, U1.26 (A9), U2.26 (A9)
/PC10: J1.11, U1.23 (A10), U2.23 (A10)
/PC11: J1.12, U1.25 (A11), U2.25 (A11)
/PC12: J1.13, U1.4 (A12), U2.4 (A12)
/PC13: J1.14, U1.28 (A13), U2.28 (A13)
/PC14: J1.15, U1.29 (A14), U2.29 (A14)
/PC15: J1.16, U1.3 (A15), U2.3 (A15)
/RAMEN_R: J2.18, U1.24 (OE), U2.24 (OE)
GND: C1.2, C2.2, J1.17, U1.2 (A16), U1.16 (GND), U2.2 (A16), U2.16 (GND)
VCC: C1.1, C2.1, J1.18, U1.31 (PGM), U1.32 (VCC), U2.31 (PGM), U2.32 (VCC)

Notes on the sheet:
RAMEN_R enables the ROM. The right side of the RAM is used for Instruction Fetch. If the IF stage is not being fed by RAM then it is being fed by this ROM.
Each ROM is socketed SST39SF010A, or equivalent.

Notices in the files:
Hardware/PrototypeProcessor/RegisterFileModule/RegisterFileModule.kicad_pcb:
Copyright © 2022-2023 Andrew Fox
MEMModule-NoROM/MEMModule.kicad_pcb:
Copyright © 2022 Andrew Fox
MainBoard.kicad_pcb:
Turtle16 © 2020 Andrew Fox, Rev 1
